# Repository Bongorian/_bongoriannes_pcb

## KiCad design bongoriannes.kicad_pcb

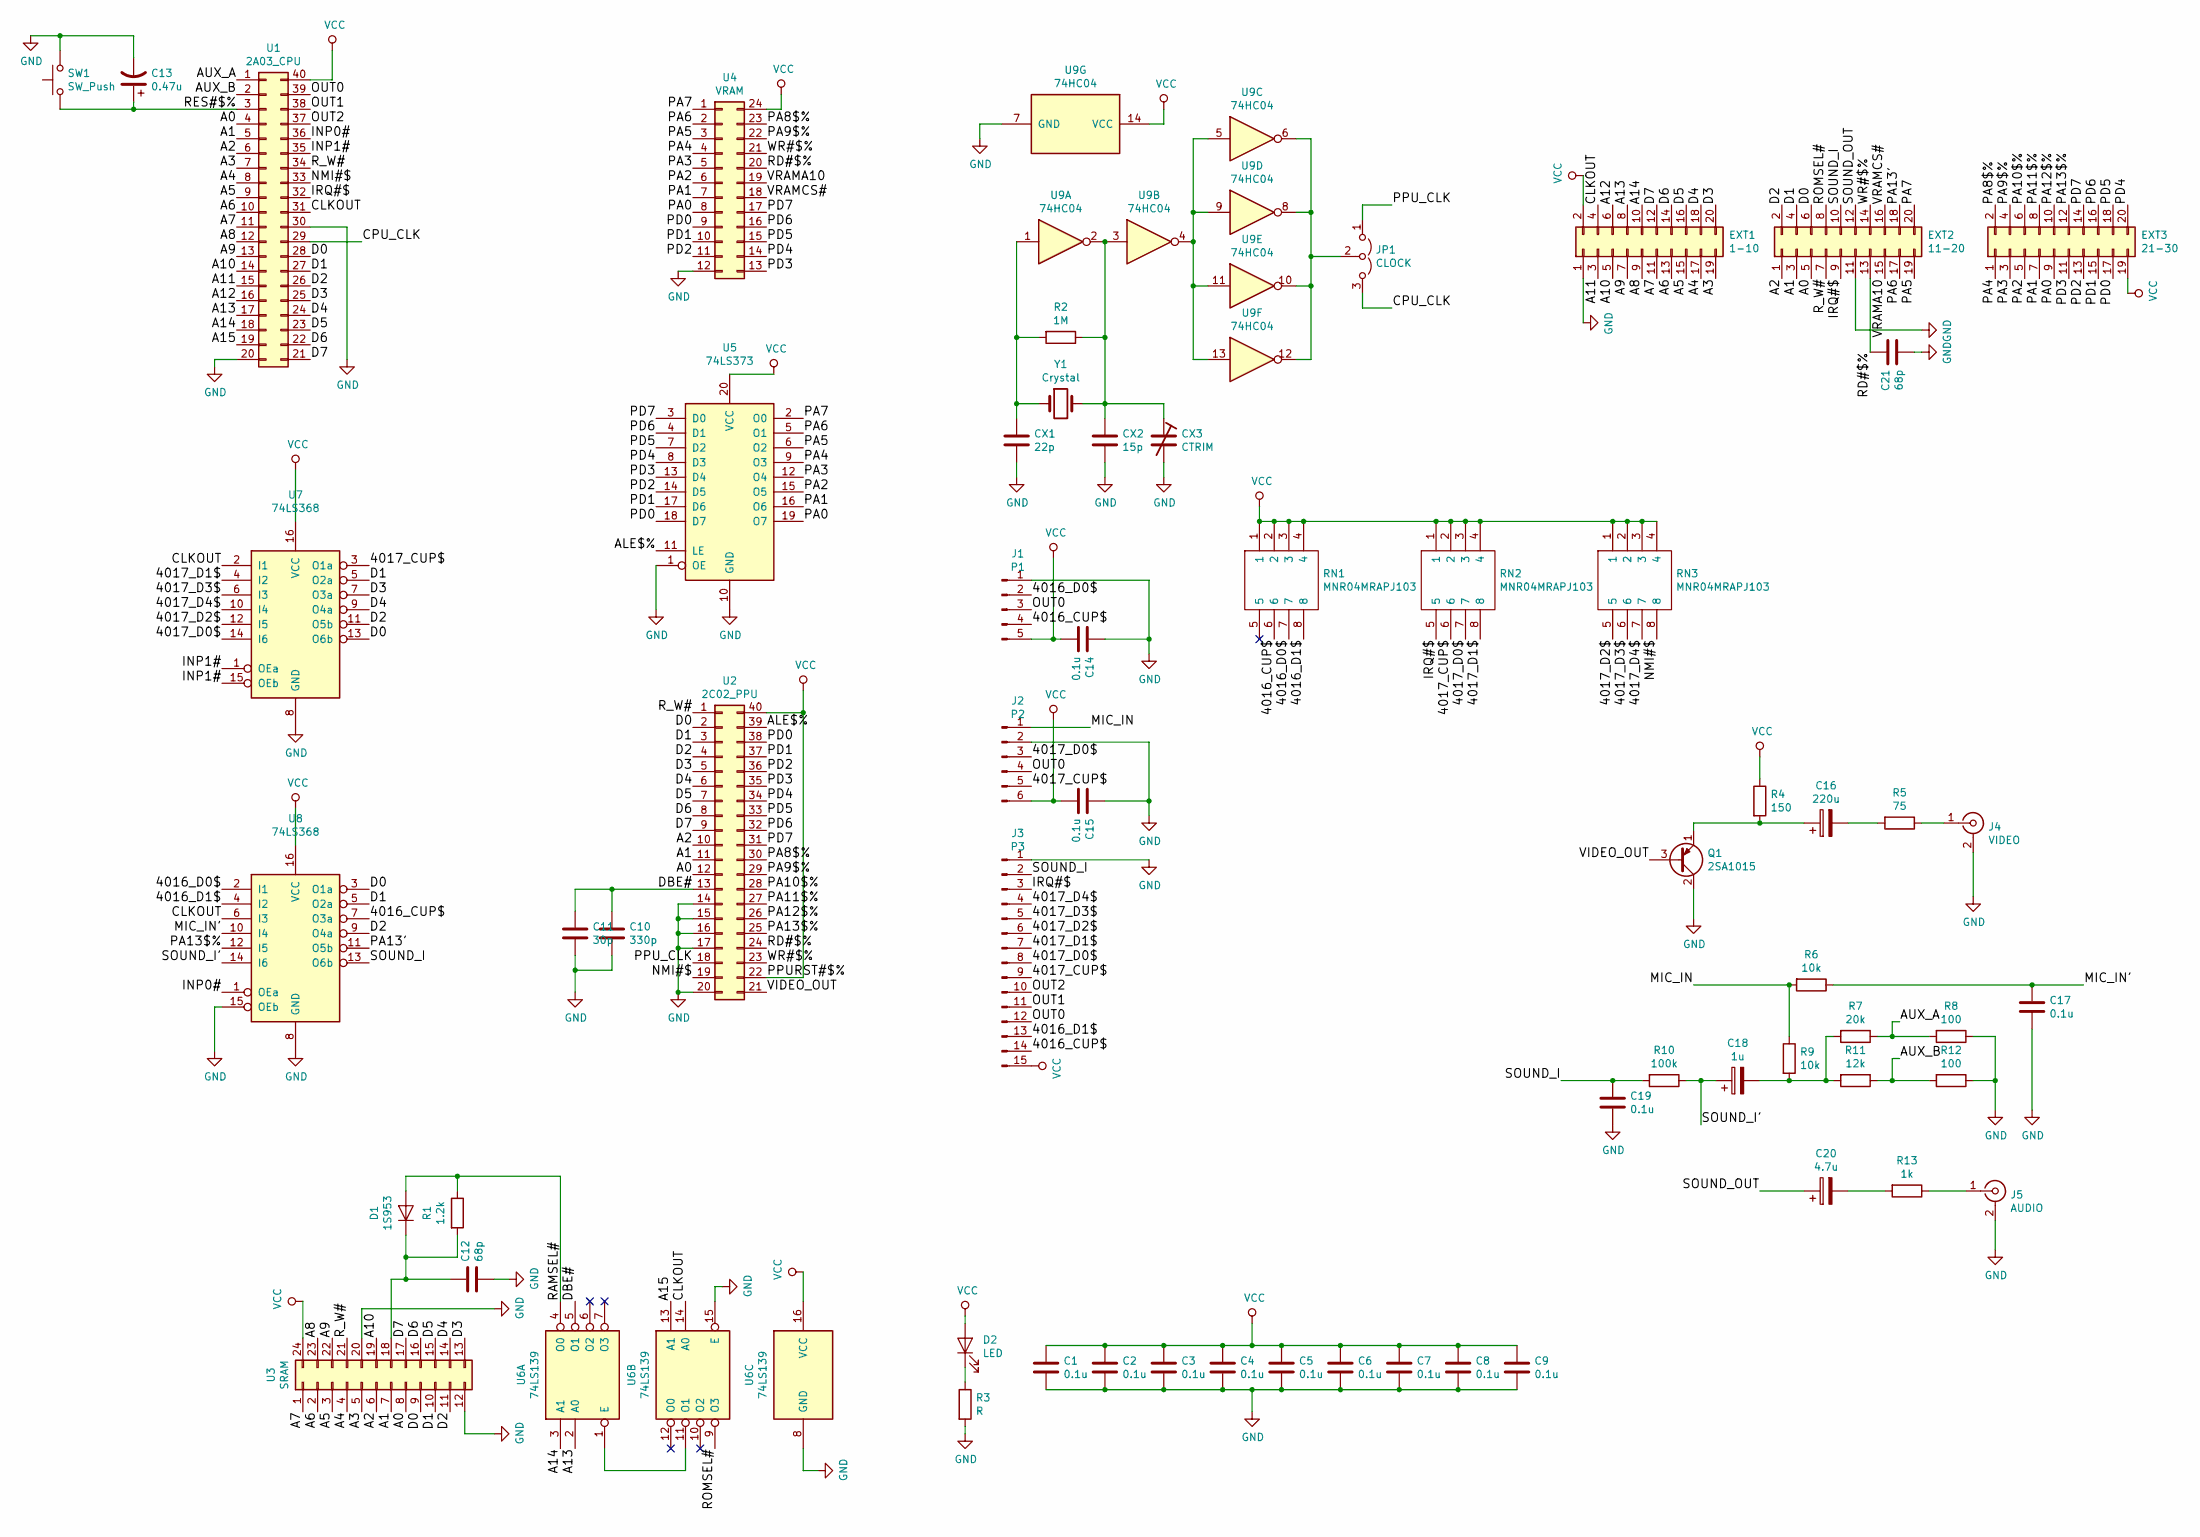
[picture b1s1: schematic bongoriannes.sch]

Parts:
C1, C2, C3, C4, C5, C6, C7, C8, C9: 0.1u; C_0805_2012Metric_Pad1.15x1.40mm_HandSolder
C10: 330p; C_Disc_D3.0mm_W1.6mm_P2.50mm
C11: 30p; C_Disc_D3.0mm_W1.6mm_P2.50mm
C12, C21: 68p; C_Disc_D3.0mm_W1.6mm_P2.50mm
C13: 0.47u; CP_Radial_D5.0mm_P2.00mm
C14, C15, C17, C19: 0.1u; C_Disc_D3.0mm_W1.6mm_P2.50mm
C16: 220u; CP_Radial_D8.0mm_P3.50mm
C18: 1u; CP_Radial_D5.0mm_P2.00mm
C20: 4.7u; CP_Radial_D5.0mm_P2.00mm
CX1: 22p; C_Disc_D3.0mm_W1.6mm_P2.50mm
CX2: 15p; C_Disc_D3.0mm_W1.6mm_P2.50mm
CX3: CTRIM; C_Trimmer_Murata_TZC3
D1: 1S953; DIODE_SHORT
D2: LED; LED_D3.0mm
EXT1: 1-10; PinHeader_2x10_P1.27mm_Vertical_SMD
EXT2: 11-20; PinHeader_2x10_P1.27mm_Vertical_SMD
EXT3: 21-30; PinHeader_2x10_P1.27mm_Vertical_SMD
J1: P1; PinHeader_1x05_P2.54mm_Vertical
J2: P2; PinHeader_1x06_P2.54mm_Vertical
J3: P3; PinHeader_1x15_P1.00mm_Vertical
J4: VIDEO; RCA_RJ2410N
J5: AUDIO; RCA_RJ2410N
JP1: CLOCK; SolderJumper-3_P1.3mm_Open_RoundedPad1.0x1.5mm
Q1: 2SA1015; TO-92_Inline
R1: 1.2k; R_Axial_DIN0204_L3.6mm_D1.6mm_P5.08mm_Horizontal
R2: 1M; R_Axial_DIN0204_L3.6mm_D1.6mm_P5.08mm_Horizontal
R3: R; R_Axial_DIN0204_L3.6mm_D1.6mm_P5.08mm_Horizontal
R4: 150; R_Axial_DIN0204_L3.6mm_D1.6mm_P5.08mm_Horizontal
R5: 75; R_Axial_DIN0204_L3.6mm_D1.6mm_P5.08mm_Horizontal
R6, R9: 10k; R_Axial_DIN0204_L3.6mm_D1.6mm_P5.08mm_Horizontal
R7: 20k; R_Axial_DIN0204_L3.6mm_D1.6mm_P5.08mm_Horizontal
R8, R12: 100; R_Axial_DIN0204_L3.6mm_D1.6mm_P5.08mm_Horizontal
R10: 100k; R_Axial_DIN0204_L3.6mm_D1.6mm_P5.08mm_Horizontal
R11: 12k; R_Axial_DIN0204_L3.6mm_D1.6mm_P5.08mm_Horizontal
R13: 1k; R_Axial_DIN0204_L3.6mm_D1.6mm_P5.08mm_Horizontal
RN1, RN2, RN3: MNR04MRAPJ103; RESCAX50P100X200X36-8N; Manufacturer_Part_Number MNR04MRAPJ103
SW1: SW_Push; PG1350
U1: 2A03_CPU; DIP-40_W15.24mm_LongPads_hoso
U2: 2C02_PPU; DIP-40_W15.24mm_LongPads_hoso
U3: SRAM; SOIC-24W_7.5x15.4mm_P1.27mm
U4: VRAM; SOIC-24W_7.5x15.4mm_P1.27mm
U5: 74LS373; SOIC-20W_7.5x12.8mm_P1.27mm
U6: 74LS139; SOIC-16_3.9x9.9mm_P1.27mm
U7, U8: 74LS368; SOIC-16_3.9x9.9mm_P1.27mm
U9: 74HC04; SOIC-14_3.9x8.7mm_P1.27mm
Y1: Crystal; Crystal_HC49-4H_Vertical

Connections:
/4016_CUP$: J1.4, J3.14, RN1.6, U8.7 (O3a)
/4016_D0$: J1.2, RN1.7, U8.2 (I1)
/4016_D1$: J3.13, RN1.8, U8.4 (I2)
/4017_CUP$: J2.5, J3.9, RN2.6, U7.3 (O1a)
/4017_D0$: J2.3, J3.8, RN2.7, U7.14 (I6)
/4017_D1$: J3.7, RN2.8, U7.4 (I2)
/4017_D2$: J3.6, RN3.5, U7.12 (I5)
/4017_D3$: J3.5, RN3.6, U7.6 (I3)
/4017_D4$: J3.4, RN3.7, U7.10 (I4)
/A0: EXT2.5, U1.4, U2.12, U3.8
/A1: EXT2.3, U1.5, U2.11, U3.7
/A2: EXT2.1, U1.6, U2.10, U3.6
/A3: EXT1.19, U1.7, U3.5
/A4: EXT1.17, U1.8, U3.4
/A5: EXT1.15, U1.9, U3.3
/A6: EXT1.13, U1.10, U3.2
/A7: EXT1.11, U1.11, U3.1
/A8: EXT1.9, U1.12, U3.23
/A9: EXT1.7, U1.13, U3.22
/A10: EXT1.5, U1.14, U3.19
/A11: EXT1.3, U1.15
/A12: EXT1.6, U1.16
/A13: EXT1.8, U1.17, U6.2 (A0)
/A14: EXT1.10, U1.18, U6.3 (A1)
/A15: U1.19, U6.13 (A1)
/ALE$%: U2.39, U5.11 (LE)
/AUX_A: R7.1, R8.2, U1.1
/AUX_B: R11.1, R12.2, U1.2
/CLKOUT: EXT1.4, U1.31, U6.14 (A0), U7.2 (I1), U8.6 (I3)
/CPU_CLK: JP1.3 (B), U1.29
/D0: EXT2.6, U1.28, U2.2, U3.9, U7.13 (O6b), U8.3 (O1a)
/D1: EXT2.4, U1.27, U2.3, U3.10, U7.5 (O2a), U8.5 (O2a)
/D2: EXT2.2, U1.26, U2.4, U3.11, U7.11 (O5b), U8.9 (O4a)
/D3: EXT1.20, U1.25, U2.5, U3.13, U7.7 (O3a)
/D4: EXT1.18, U1.24, U2.6, U3.14, U7.9 (O4a)
/D5: EXT1.16, U1.23, U2.7, U3.15
/D6: EXT1.14, U1.22, U2.8, U3.16
/D7: EXT1.12, U1.21, U2.9, U3.17
/DBE#: C10.1, C11.1, U2.13, U6.5 (O1)
/INP0#: U1.36, U8.1 (OEa)
/INP1#: U1.35, U7.1 (OEa), U7.15 (OEb)
/IRQ#$: EXT2.9, J3.3, RN2.5, U1.32
/MIC_IN: J2.1, R6.2, R9.1
/MIC_IN': C17.1, R6.1, U8.10 (I4)
/NMI#$: RN3.8, U1.33, U2.19
/OUT0: J1.3, J2.4, J3.12, U1.39
/OUT1: J3.11, U1.38
/OUT2: J3.10, U1.37
/PA0: EXT3.9, U4.8, U5.19 (O7)
/PA1: EXT3.7, U4.7, U5.16 (O6)
/PA2: EXT3.5, U4.6, U5.15 (O5)
/PA3: EXT3.3, U4.5, U5.12 (O4)
/PA4: EXT3.1, U4.4, U5.9 (O3)
/PA5: EXT2.19, U4.3, U5.6 (O2)
/PA6: EXT2.17, U4.2, U5.5 (O1)
/PA7: EXT2.20, U4.1, U5.2 (O0)
/PA8$%: EXT3.2, U2.30, U4.23
/PA9$%: EXT3.4, U2.29, U4.22
/PA10$%: EXT3.6, U2.28
/PA11$%: EXT3.8, U2.27
/PA12$%: EXT3.10, U2.26
/PA13$%: EXT3.12, U2.25, U8.12 (I5)
/PA13': EXT2.18, U8.11 (O5b)
/PD0: EXT3.17, U2.38, U4.9, U5.18 (D7)
/PD1: EXT3.15, U2.37, U4.10, U5.17 (D6)
/PD2: EXT3.13, U2.36, U4.11, U5.14 (D5)
/PD3: EXT3.11, U2.35, U4.13, U5.13 (D4)
/PD4: EXT3.20, U2.34, U4.14, U5.8 (D3)
/PD5: EXT3.18, U2.33, U4.15, U5.7 (D2)
/PD6: EXT3.16, U2.32, U4.16, U5.4 (D1)
/PD7: EXT3.14, U2.31, U4.17, U5.3 (D0)
/PPU_CLK: JP1.1 (A), U2.18
/RAMSEL#: D1.2 (A), R1.1, U6.4 (O0)
/RD#$%: C21.1, EXT2.13, U2.24, U4.20
/RES#$%: C13.1, SW1.1, U1.3
/ROMSEL#: EXT2.8, U6.9 (O3)
/R_W#: EXT2.7, U1.34, U2.1, U3.21
/SOUND_I: C19.1, EXT2.10, J3.2, R10.2, U8.13 (O6b)
/SOUND_I': C18.1, R10.1, U8.14 (I6)
/SOUND_OUT: C20.1, EXT2.12
/VIDEO_OUT: Q1.3 (B), U2.21
/VRAMA10: EXT2.15, U4.19
/VRAMCS#: EXT2.16, U4.18
/WR#$%: EXT2.14, U2.23, U4.21
GND: C1.2, C2.2, C3.2, C4.2, C5.2, C6.2, C7.2, C8.2, C9.2, C10.2, C11.2, C12.2, C13.2, C14.1, C15.1, C17.2, C19.2, C21.2, CX1.2, CX2.2, CX3.2, EXT1.1, EXT2.11, J1.1, J2.2, J3.1, J4.2 (Ext), J5.2 (Ext), Q1.2 (C), R3.2, R8.1, R12.1, SW1.2, U1.20, U1.30, U2.14, U2.15, U2.16, U2.17, U2.20, U3.12, U3.20, U4.12, U5.1 (OE), U5.10 (GND), U6.8 (GND), U6.15 (E), U7.8 (GND), U8.8 (GND), U8.15 (OEb), U9.7 (GND)
unnamed: C12.1, D1.1 (K), R1.2, U3.18
unnamed: C16.1, Q1.1 (E), R4.2
unnamed: C16.2, R5.2
unnamed: C18.2, R7.2, R9.2, R11.2
unnamed: C20.2, R13.2
unnamed: CX1.1, R2.2, U9.1, Y1.1
unnamed: CX2.1, CX3.1, R2.1, U9.2, U9.3, Y1.2
unnamed: D2.1 (K), R3.1
unnamed: J4.1 (In), R5.1
unnamed: J5.1 (In), R13.1
unnamed: JP1.2 (C), U9.6, U9.8, U9.10, U9.12
unnamed: U6.1 (E), U6.11 (O1)
unnamed: U9.4, U9.5, U9.9, U9.11, U9.13
VCC: C1.1, C2.1, C3.1, C4.1, C5.1, C6.1, C7.1, C8.1, C9.1, C14.2, C15.2, D2.2 (A), EXT1.2, EXT3.19, J1.5, J2.6, J3.15, R4.1, RN1.1, RN1.2, RN1.3, RN1.4, RN2.1, RN2.2, RN2.3, RN2.4, RN3.1, RN3.2, RN3.3, RN3.4, U1.40, U2.22, U2.40, U3.24, U4.24, U5.20 (VCC), U6.16 (VCC), U7.16 (VCC), U8.16 (VCC), U9.14 (VCC)

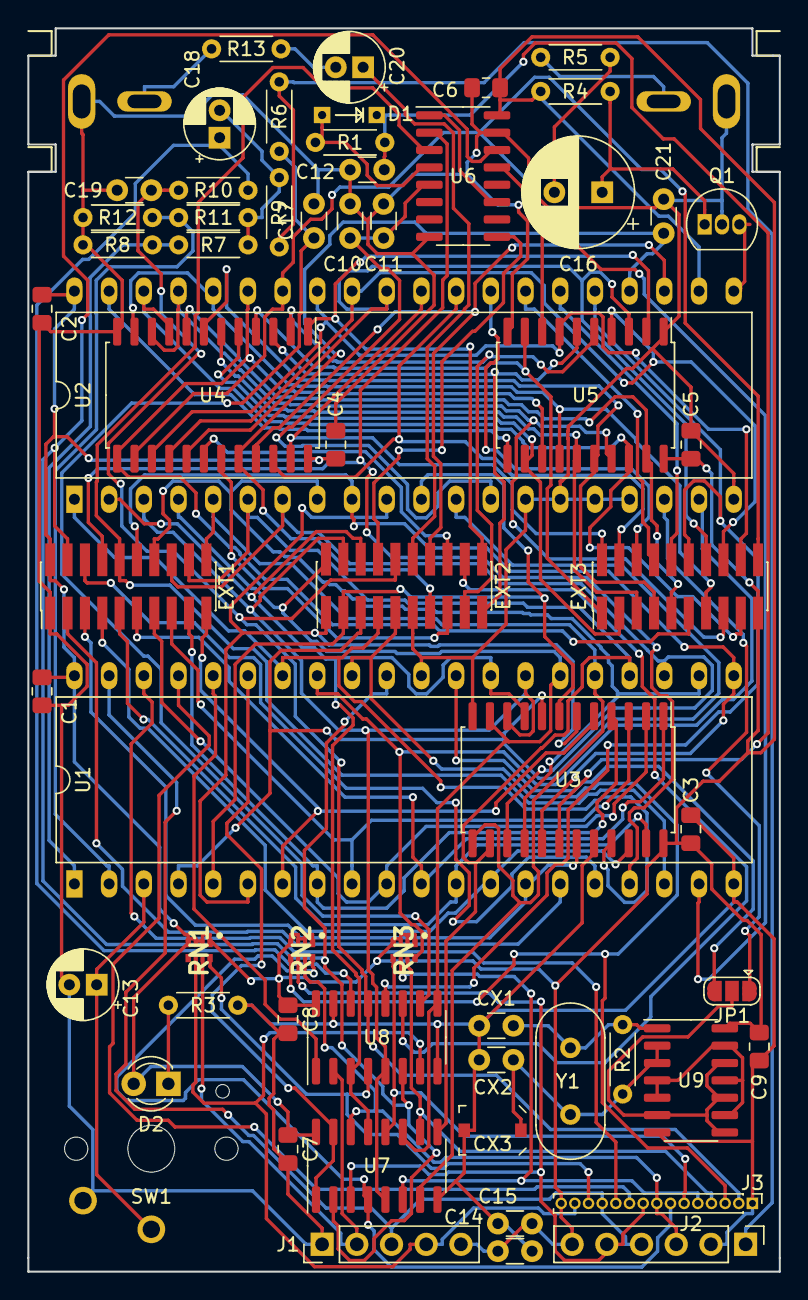
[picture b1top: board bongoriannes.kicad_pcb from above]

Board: 2 copper layers, 55.0 x 91.0 mm, 63 parts (0 on the bottom side), 99 nets.

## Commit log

2019-07-24 clean
2019-07-29 meishi_size
